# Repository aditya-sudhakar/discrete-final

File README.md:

# discrete-final
PCB auto-placement algorithm

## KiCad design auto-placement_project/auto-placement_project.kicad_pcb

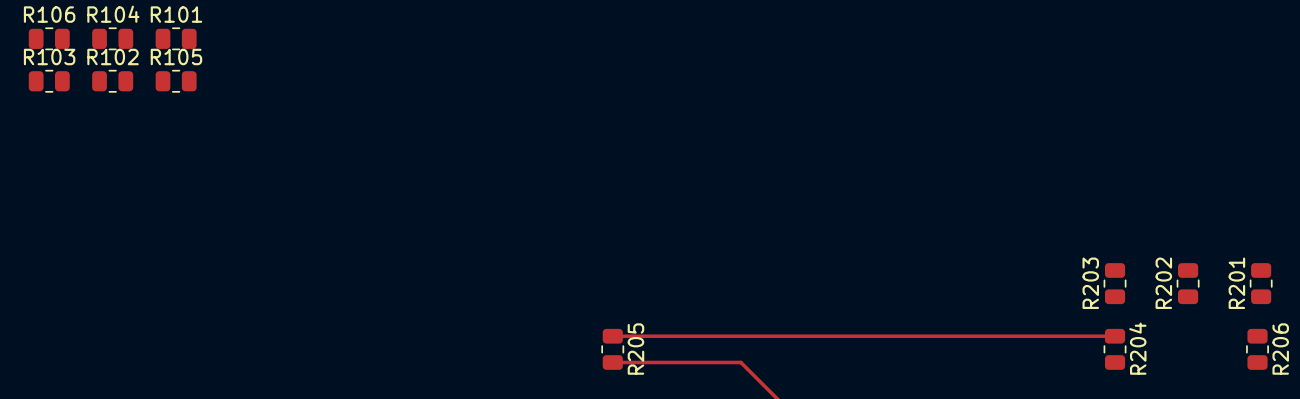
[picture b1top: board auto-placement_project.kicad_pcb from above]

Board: 2 copper layers, 12 parts (0 on the bottom side), 3 nets.

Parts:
R101, R102, R103, R104, R105, R106, R201, R202, R203, R204, R205, R206: R; R_0805_2012Metric

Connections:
/RES_COMMON: R101.2, R102.2, R103.2, R104.1, R105.1, R106.1, R201.2, R202.2, R203.2, R204.1, R205.1, R206.1
/RES_HIGH_SIDE: R101.1, R102.1, R103.1, R201.1, R202.1, R203.1
/RES_LOW_SIDE: R104.2, R105.2, R106.2, R204.2, R205.2, R206.2

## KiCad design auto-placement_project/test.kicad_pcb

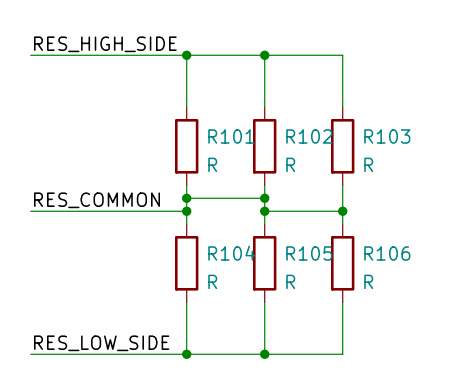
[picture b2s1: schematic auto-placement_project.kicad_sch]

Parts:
R101, R102, R103, R104, R105, R106: R; R_0805_2012Metric

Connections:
/RES_COMMON: R101.2, R102.2, R103.2, R104.1, R105.1, R106.1
/RES_HIGH_SIDE: R101.1, R102.1, R103.1
/RES_LOW_SIDE: R104.2, R105.2, R106.2

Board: 2 copper layers, 6 parts (0 on the bottom side), 3 nets, no tracks yet.

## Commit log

2021-12-06 initial commit of kicad files
2021-12-06 adding gitignore
2021-12-09 implemented min graph thickness
2021-12-09 added calculate grid length function
2021-12-09 Created a README file
2021-12-09 tidying up
2021-12-11 implemented .pcb file consumption function
2021-12-11 can fully manipulate circuit and move objects in pcb file
2021-12-14 first pass working mvp
2021-12-15 commented some functions
